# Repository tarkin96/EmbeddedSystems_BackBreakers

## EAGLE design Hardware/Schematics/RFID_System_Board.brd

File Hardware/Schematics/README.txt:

Team: Back Breakers
Team Mebers: Joe Hilbert, Keven Fuentes, Wade King
Repo URL: buffet@buffet.cs.clemson.edu:kfuente/BackBreakers-CPSC4820

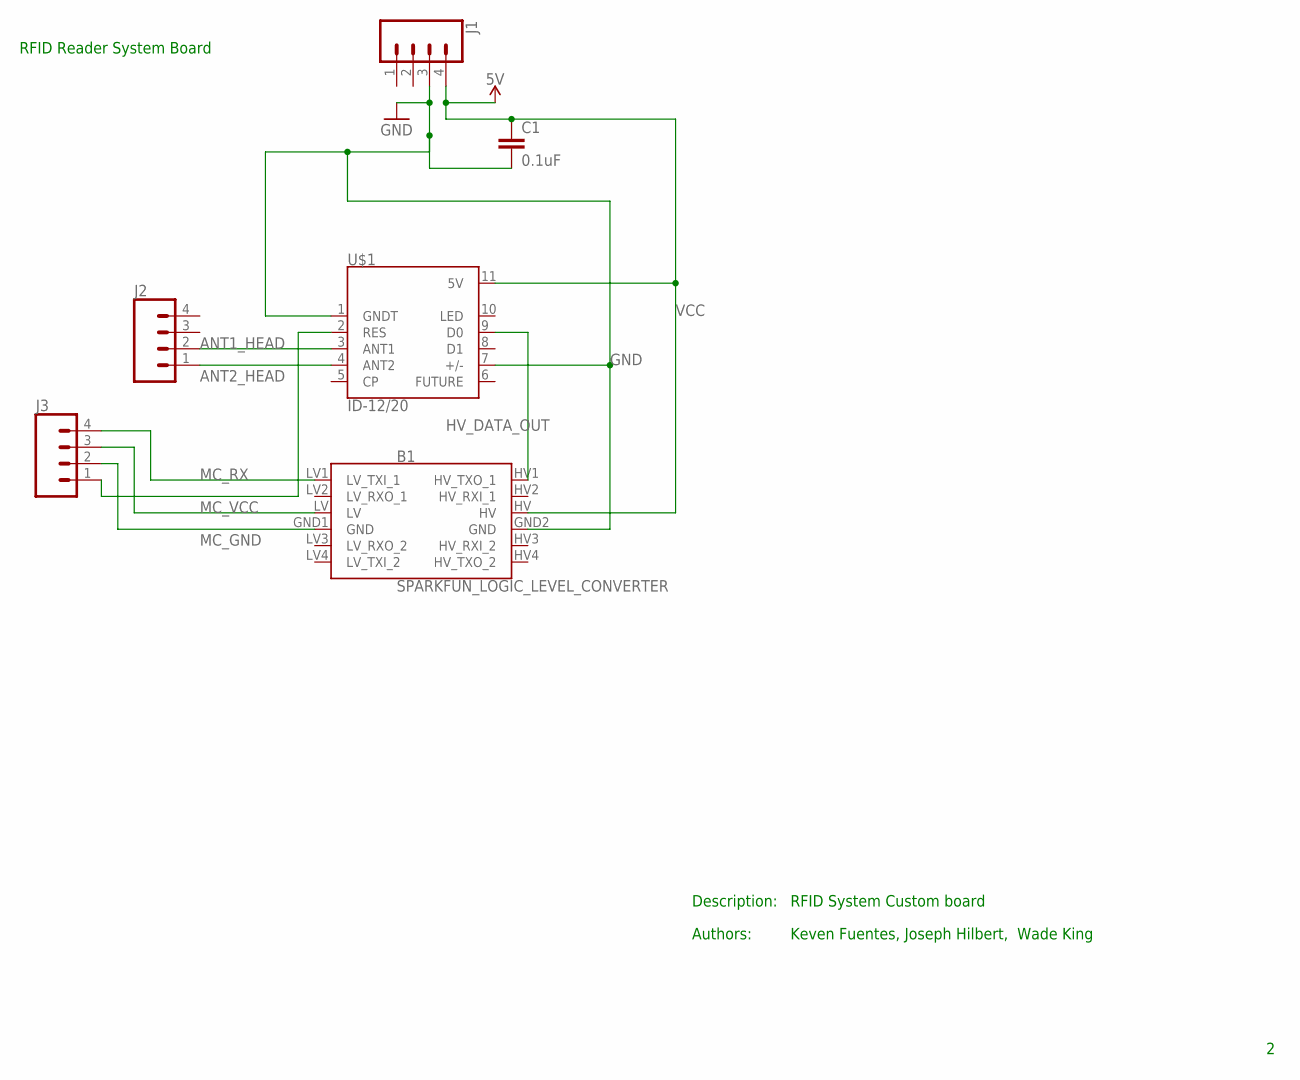
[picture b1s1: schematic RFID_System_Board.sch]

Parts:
B1: SPARKFUN_LOGIC_LEVEL_CONVERTER
C1: 0.1uF; 0603
J1, J2, J3: CONN_04; 1X04
U$1: ID-12/20; ID-12

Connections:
ANT1_HEAD: J2.2, U$1.3 (ANT1)
ANT2_HEAD: J2.1, U$1.4 (ANT2)
GND: B1.GND2 (GND), C1.2, J1.3, U$1.1 (GNDT), U$1.7 (+/-)
HV_DATA_OUT: B1.HV1 (HV_TXO_1), U$1.9 (D0)
MC_GND: B1.GND1 (GND), J3.2
MC_RX: B1.LV1 (LV_TXI_1), J3.4
MC_VCC: B1.LV, J3.3
unnamed: J3.1, U$1.2 (RES)
VCC: B1.HV, C1.1, J1.4, U$1.11 (5V)

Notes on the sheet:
RFID Reader System Board
RFID System Custom board
Keven Fuentes, Joseph Hilbert, Wade King
Description:
Authors:

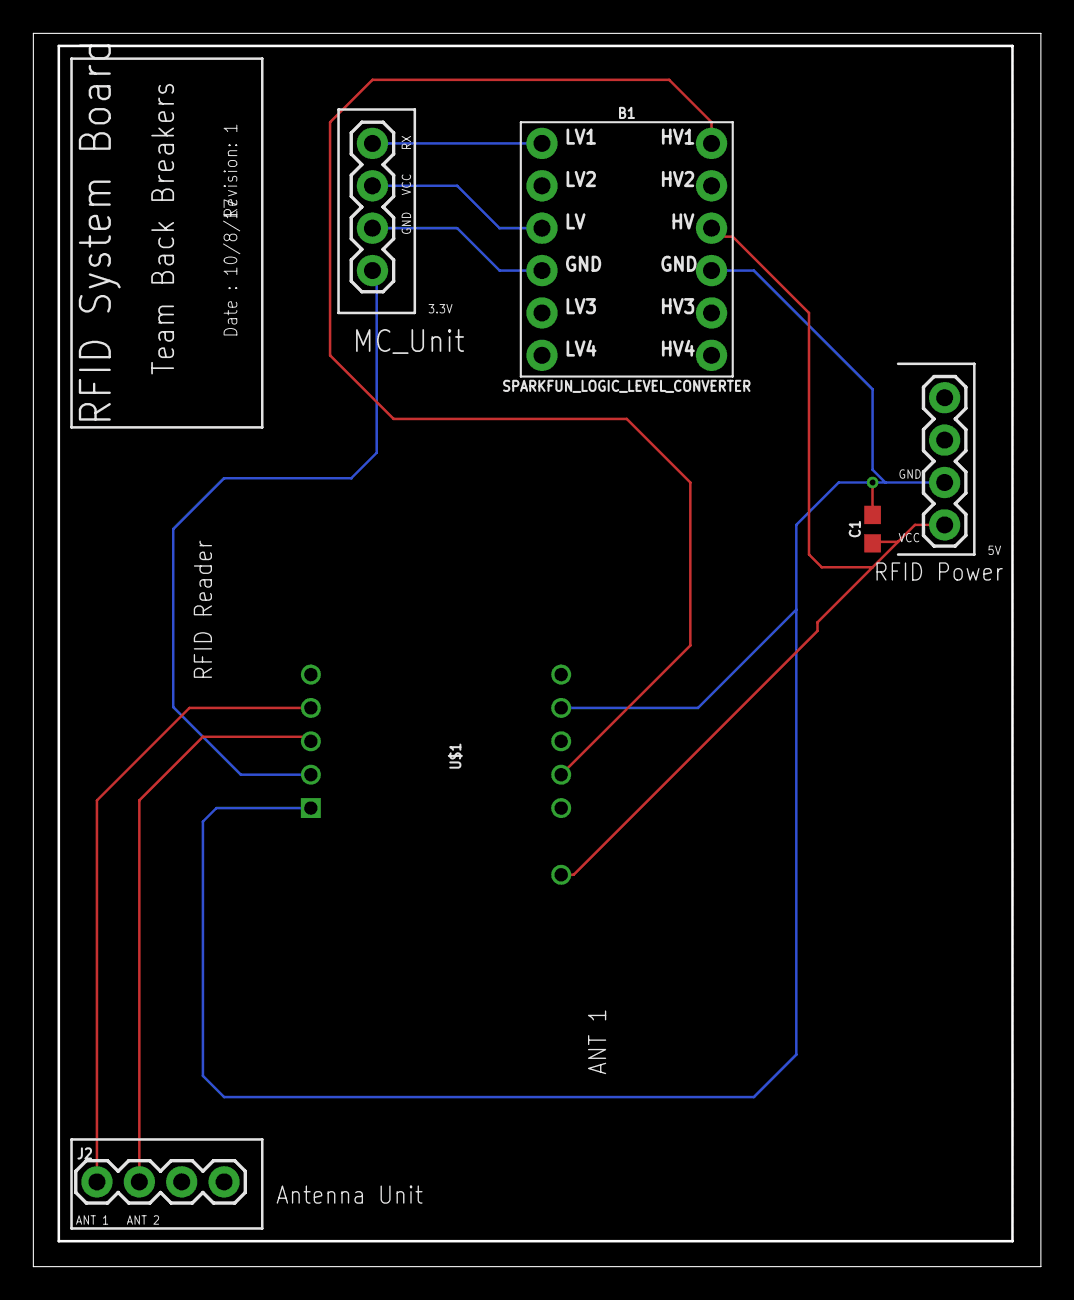
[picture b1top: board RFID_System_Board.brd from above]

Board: 2 copper layers, 60.4 x 73.9 mm, 6 parts (0 on the bottom side), 9 nets.

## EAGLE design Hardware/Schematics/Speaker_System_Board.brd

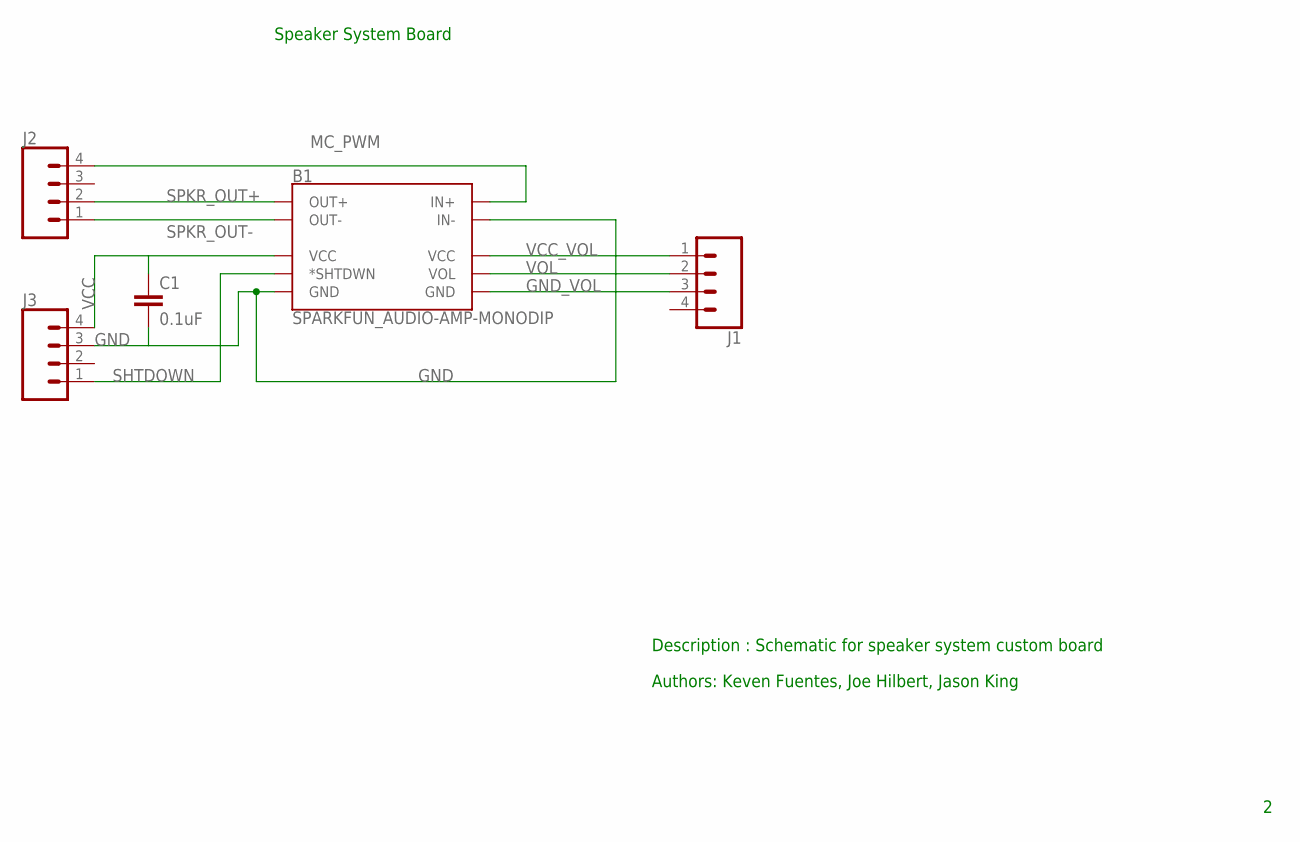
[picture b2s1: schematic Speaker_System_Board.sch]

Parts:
B1: SPARKFUN_AUDIO-AMP-MONODIP; AUDIO-AMP-MONO
C1: 0.1uF; 0603
J1, J2, J3: CONN_04; 1X04

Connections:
GND: B1.IN-, B1.PWR- (GND), C1.2, J3.3
GND_VOL: B1.VOL- (GND), J1.3
MC_PWM: B1.IN+, J2.4
SHTDOWN: B1.S (*SHTDWN), J3.1
SPKR_OUT+: B1.OUT+, J2.2
SPKR_OUT-: B1.OUT-, J2.1
VCC: B1.PWR+ (VCC), C1.1, J3.4
VCC_VOL: B1.VOL+ (VCC), J1.1
VOL: B1.VOL, J1.2

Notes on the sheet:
Speaker System Board
Description : Schematic for speaker system custom board
Authors: Keven Fuentes, Joe Hilbert, Jason King

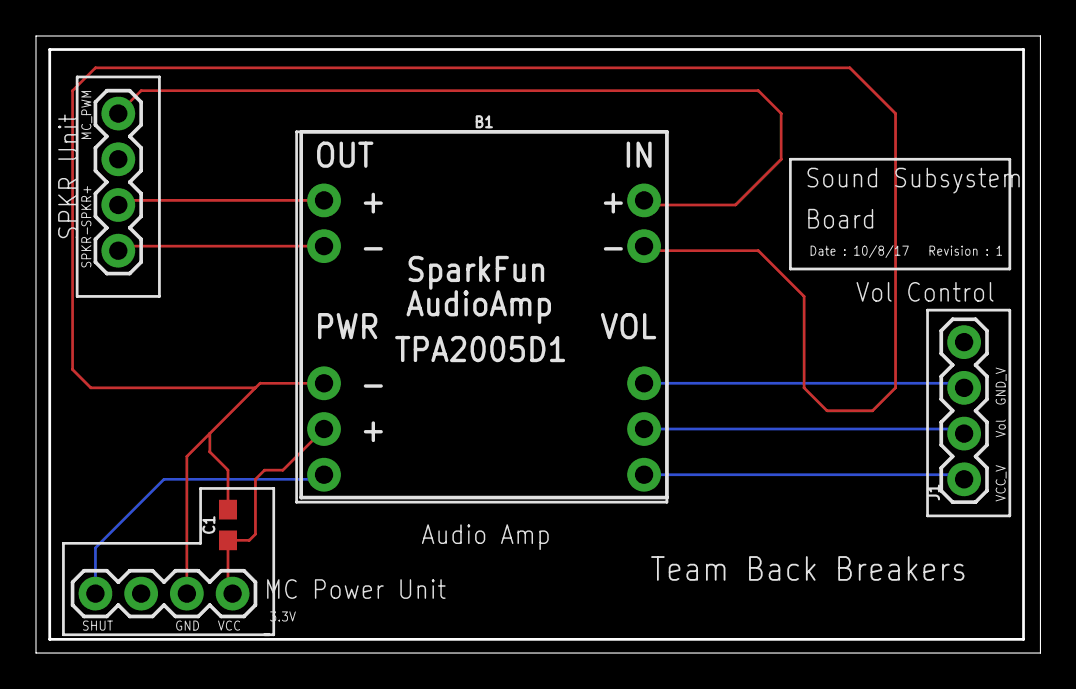
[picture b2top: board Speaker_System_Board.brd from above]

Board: 2 copper layers, 55.8 x 34.3 mm, 5 parts (0 on the bottom side), 9 nets.

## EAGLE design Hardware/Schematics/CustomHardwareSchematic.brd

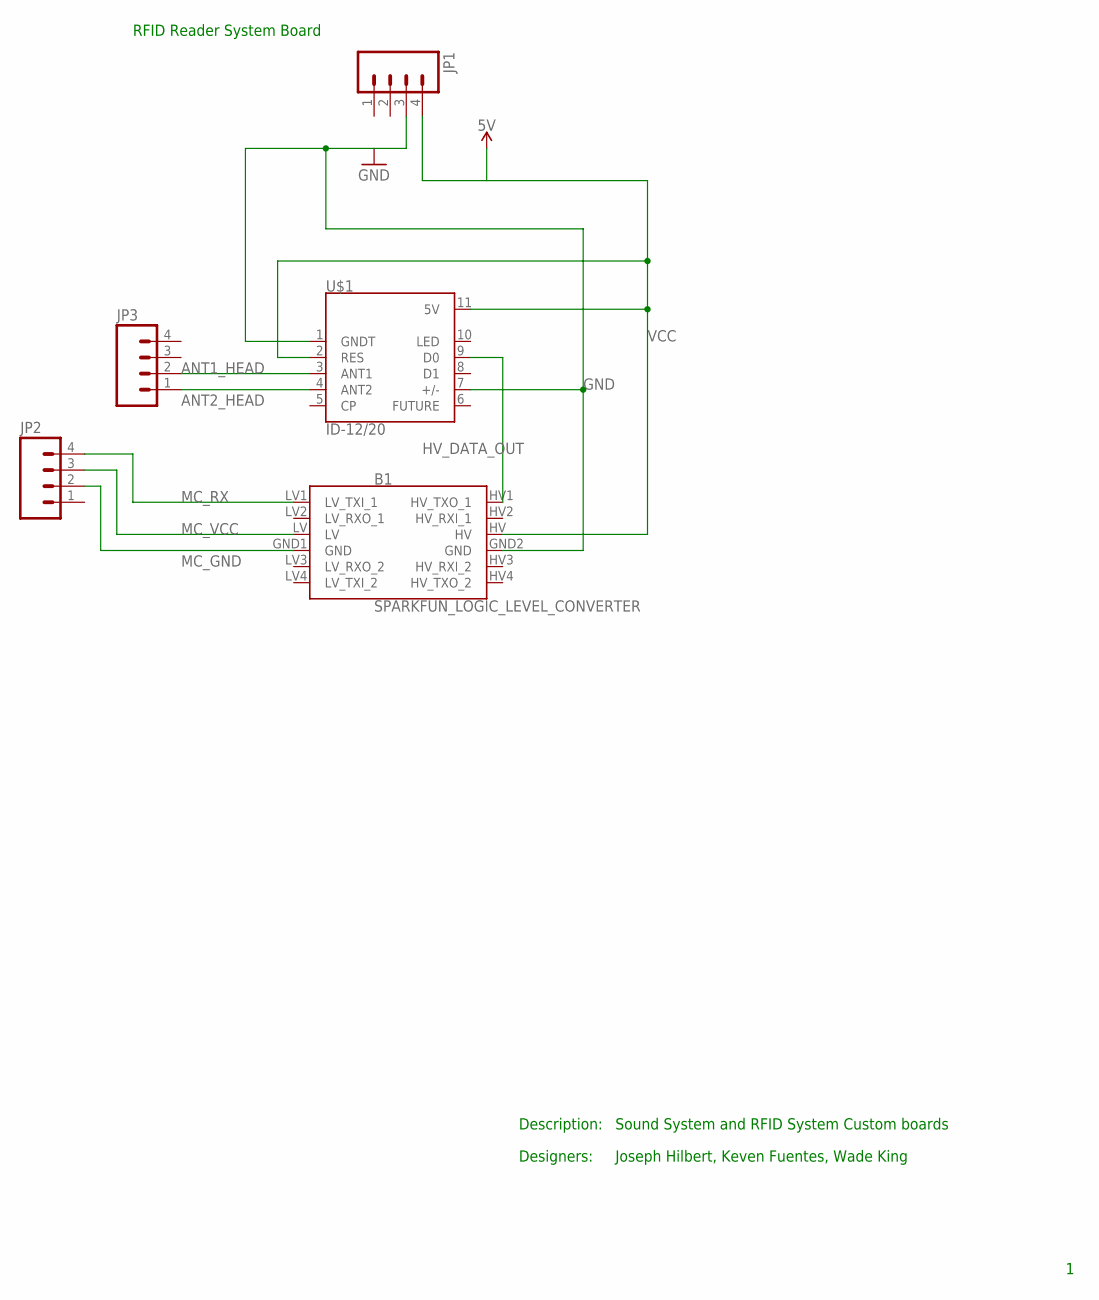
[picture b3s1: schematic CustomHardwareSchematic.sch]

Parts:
B1: SPARKFUN_LOGIC_LEVEL_CONVERTER
JP1, JP2, JP3: M04LOCK; 1X04_LOCK
U$1: ID-12/20; ID-12

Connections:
ANT1_HEAD: JP3.2, U$1.3 (ANT1)
ANT2_HEAD: JP3.1, U$1.4 (ANT2)
GND: B1.GND2 (GND), JP1.3, U$1.1 (GNDT), U$1.7 (+/-)
HV_DATA_OUT: B1.HV1 (HV_TXO_1), U$1.9 (D0)
MC_GND: B1.GND1 (GND), JP2.2
MC_RX: B1.LV1 (LV_TXI_1), JP2.4
MC_VCC: B1.LV, JP2.3
VCC: B1.HV, JP1.4, U$1.2 (RES), U$1.11 (5V)

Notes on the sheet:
RFID Reader System Board
Sound System and RFID System Custom boards
Joseph Hilbert, Keven Fuentes, Wade King
Description:
Designers:

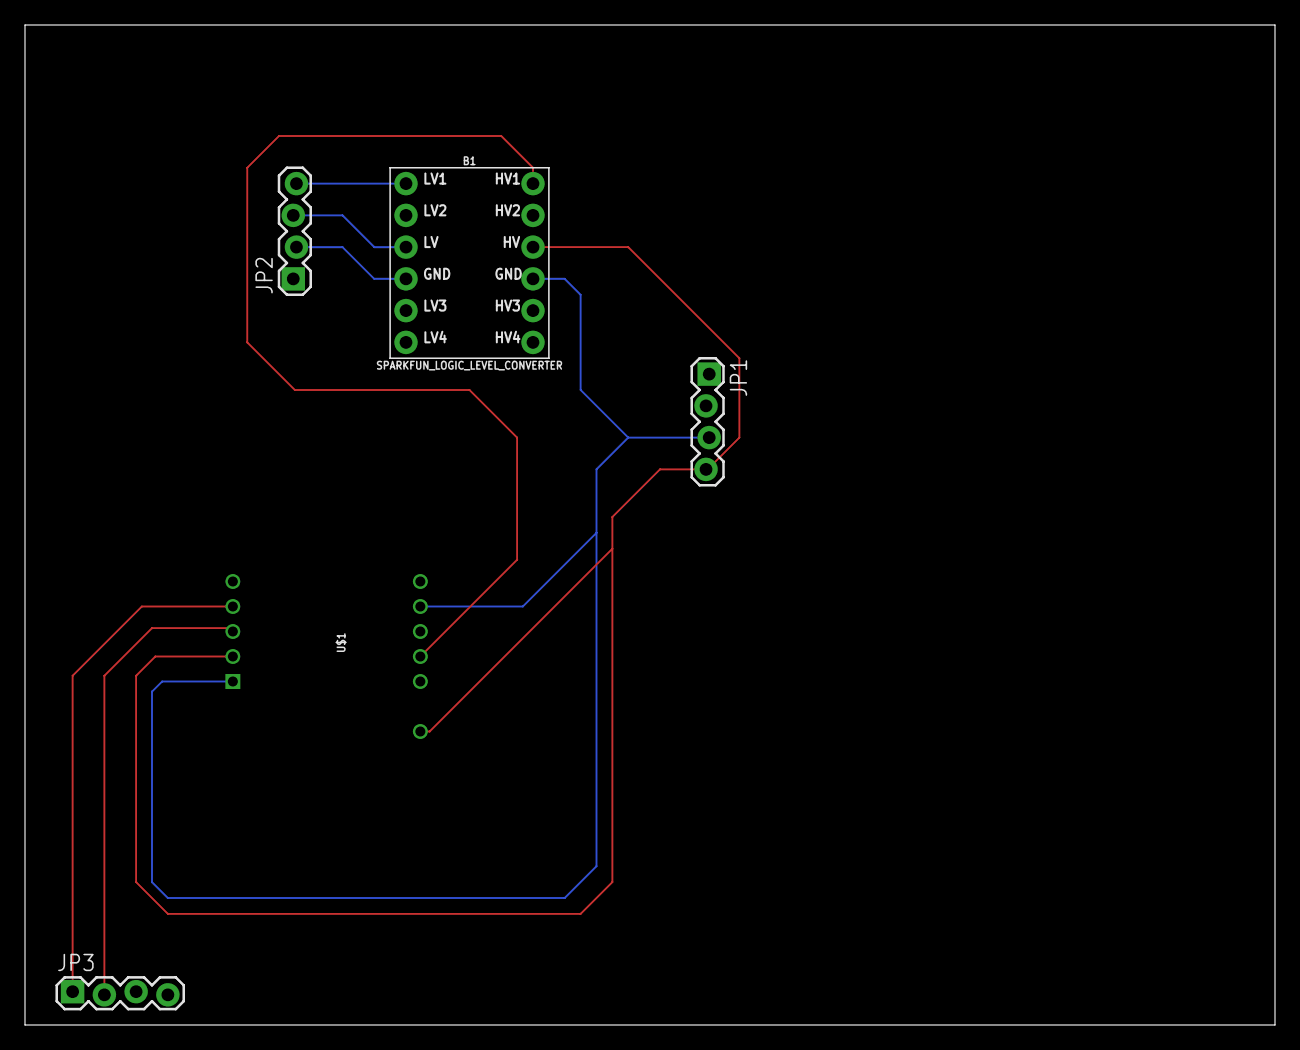
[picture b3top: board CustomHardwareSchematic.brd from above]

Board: 2 copper layers, 100.0 x 80.0 mm, 5 parts (0 on the bottom side), 8 nets.

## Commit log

2018-05-08 moving to GitHub

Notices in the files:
parts and their libraries:
SparkFun-RF: Licensing: Creative Commons ShareAlike 4.0 International - https://creativecommons.org/licenses/by-sa/4.0
